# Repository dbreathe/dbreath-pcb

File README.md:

# dbreath-pcb

Created in EagleCad by Skip Xtian.

Program using a CP210x USB to Serial convertor.
The square on the silk screen around a pin denotes GND Pins.

To put the ESP8266 into Flash mode you must hold the "Flash" button down
before powering the unit/connecting to USB.

The 5 pin header near the GAS sensor allows you to connect the LED/OLED
break out board.

Verion 1 is very basic.
DHT 22 = Pin 13
GAS = ADC
You can also use the flash button on Pin 0

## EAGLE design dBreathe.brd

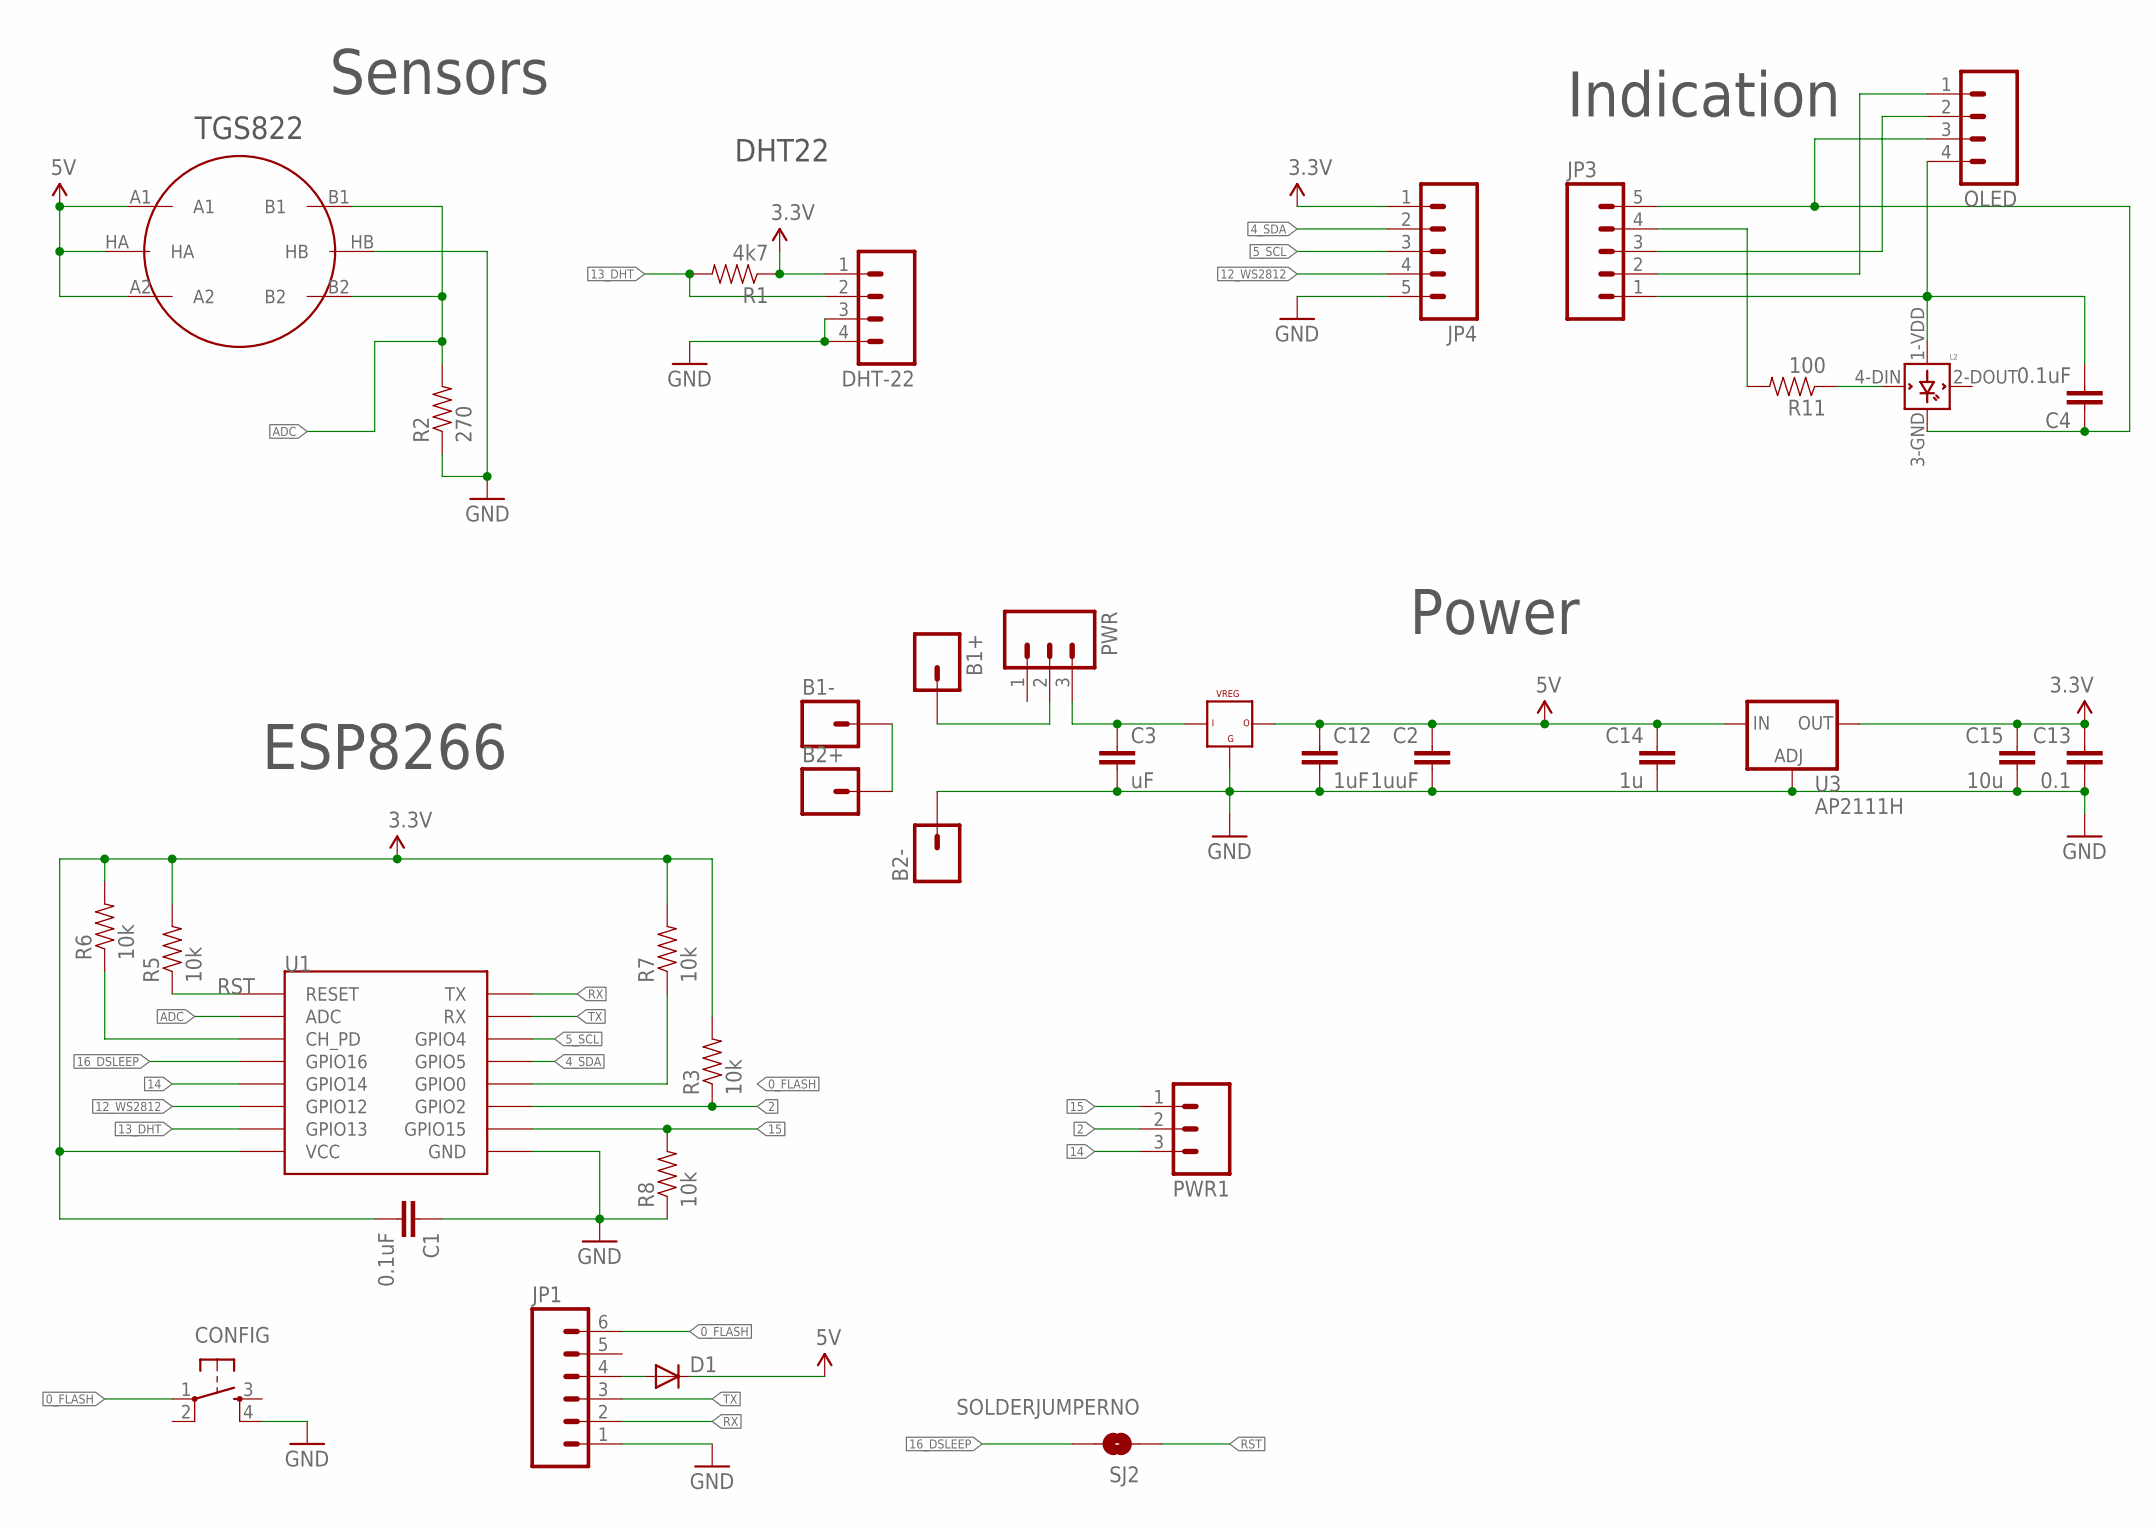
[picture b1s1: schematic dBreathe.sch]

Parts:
B1+, B1-, B2+, B2-: M01PTH; 1X01
C1, C4: 0.1uF; 0805
C2: 1uuF; 0805
C3: uF; 0805
C12: 1uF; 0805
C13: 0.1; 0805
C14: 1u; 0805
C15: 10u; 0805-CAP
CONFIG: TAC_SWITCHSMD; TACTILE_SWITCH_SMD
D1: DIODESOD; SOD-323
DHT-22: M04PTH; 1X04
JP1: M06NO_SILK_FEMALE_PTH; 1X06_NO_SILK
JP3, JP4: M05PTH; 1X05
L2: WS2812B
OLED: M041X04_NO_SILK; 1X04_NO_SILK
PWR, PWR1: M03PTH; 1X03
R1: 4k7; 0805
R2: 270; 0805
R3, R5, R6, R7, R8: 10k; 0805
R11: 100; 0805
SJ2: SOLDERJUMPERNO; SJ_2S-NO
U1: ESP12SMD; ESP12-SMD
U3: AP2111H; SOT223
U$4: VREG_5V; DPACK
U$7: METHANE_SENSOR; MQ-3

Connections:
0_FLASH: CONFIG.1, JP1.6, R7.1, U1.GPIO0
2: PWR1.2, R3.1, U1.GPIO2
3.3V: C1.2, C13.1, C15.1, DHT-22.1, JP4.1, R1.1, R3.2, R5.2, R6.2, R7.2, U1.VCC, U3.2 (OUT)
3V3_1: C4.2, JP3.1, L2.1-VDD (VDD), OLED.4
4_SDA: JP4.2, U1.GPIO5
4_SDA_1: JP3.2, OLED.1
5V: C2.1, C12.1, C14.1, D1.1 (C), U3.3 (IN), U$4.3, U$7.A1, U$7.A2, U$7.HA
5_SCL: JP4.3, U1.GPIO4
5_SCL_1: JP3.3, OLED.2
12_WS2812: JP4.4, U1.GPIO12
12_WS2812_1: JP3.4, R11.2
13_DHT: DHT-22.2, R1.2, U1.GPIO13
14: PWR1.3, U1.GPIO14
15: PWR1.1, R8.2, U1.GPIO15
16_DSLEEP: SJ2.2, U1.GPIO16
ADC: R2.2, U1.ADC, U$7.B1, U$7.B2
CH_PD: R6.1, U1.CH_PD
GND: B2-.1, C1.1, C2.2, C3.2, C12.2, C13.2, C14.2, C15.2, CONFIG.4, DHT-22.3, DHT-22.4, JP1.1, JP4.5, R2.1, R8.1, U1.GND, U3.1 (ADJ), U$4.2, U$7.HB
GND_1: C4.1, JP3.5, L2.3-GND (GND), OLED.3
unnamed: D1.2 (A), JP1.4
unnamed: B1+.1, PWR.2
unnamed: L2.4-DIN (DIN), R11.1
unnamed: B1-.1, B2+.1
RST: R5.1, SJ2.1, U1.RESET
RX: JP1.2, U1.TXD0 (TX)
TX: JP1.3, U1.RXD0 (RX)
VCC: C3.1, PWR.3, U$4.1

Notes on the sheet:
DHT22
Indication
Sensors
Power
ESP8266
TGS822

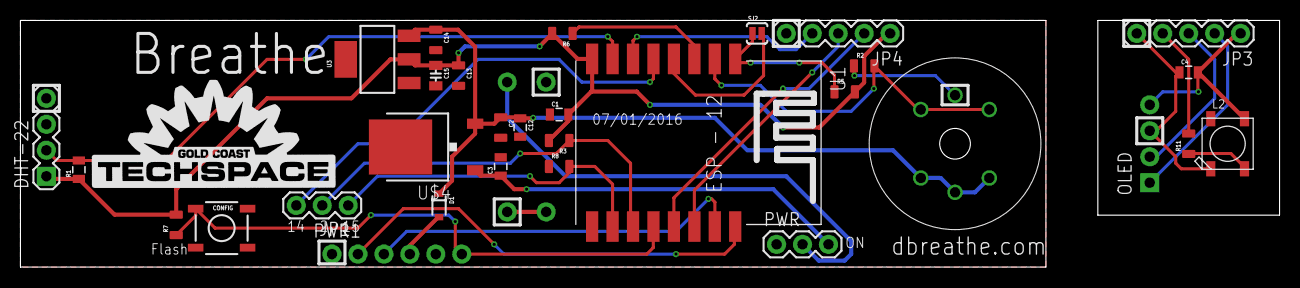
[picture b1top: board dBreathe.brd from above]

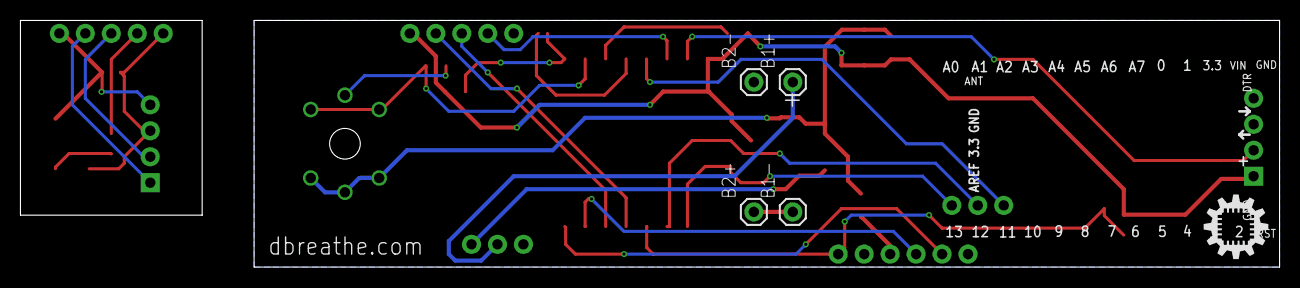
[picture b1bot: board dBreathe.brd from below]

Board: 2 copper layers, 123.2 x 24.1 mm, 37 parts (5 on the bottom side), 27 nets.

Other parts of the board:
U$1: GCTS_X0.5_TSILK
U$15: ID_LOGO_X0.25

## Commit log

2016-07-14 Version 1 of the prototype PCB

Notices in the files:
parts and their libraries:
SparkFun-Connectors: Licensing: CC v3.0 Share-Alike You are welcome to use this library for commercial purposes.
